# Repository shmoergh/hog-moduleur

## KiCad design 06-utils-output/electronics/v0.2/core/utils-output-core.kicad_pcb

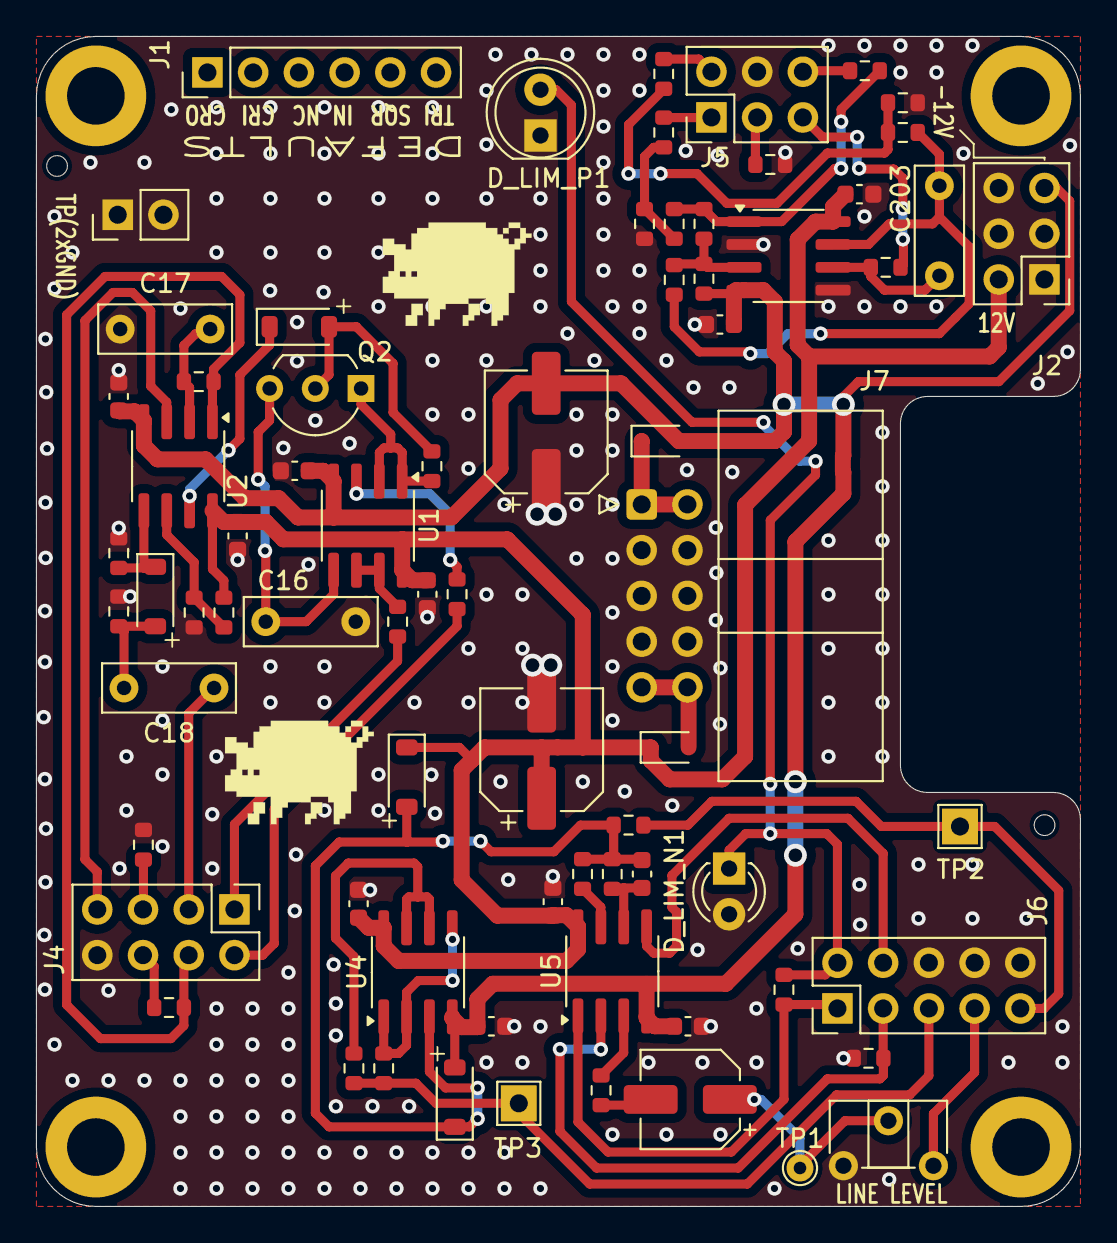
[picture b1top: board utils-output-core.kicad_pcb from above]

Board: 2 copper layers, 58.0 x 65.0 mm, 77 parts (0 on the bottom side), 48 nets.

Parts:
C1, C2, C3, C4, C10, C11, C12, C13, C201, C202: 100n; C_0603_1608Metric
C8, C9: 100u; CP_Elec_6.3x7.7
C14: 10u; CP_Elec_5x5.4
C15: 100p; C_0603_1608Metric
C16, C17: 100n (foil); C_Rect_L7.2mm_W2.5mm_P5.00mm_FKS2_FKP2_MKS2_MKP2
C18: 1n (foil); C_Rect_L7.2mm_W2.5mm_P5.00mm_FKS2_FKP2_MKS2_MKP2
C203: 3.3n (foil); C_Rect_L7.0mm_W2.5mm_P5.00mm
D1, D2: 1N5817; D_SOD-323
D3, D4, D15, D16: 1N4148; D_SOD-123
D_LIM_N1: Red LED; LED_D3.0mm
D_LIM_P1: Red LED; LED_D5.0mm
H1, H2, H3, H4: MountingHole; MountingHole_3.2mm_M3_DIN965_Pad
J1: Conn_01x06; PinHeader_1x06_P2.54mm_Vertical
J2, J5: Conn_02x03_Odd_Even; PinHeader_2x03_P2.54mm_Vertical
J3: Conn_01x02; PinHeader_1x02_P2.54mm_Vertical
J4: Conn_02x04_Odd_Even; PinHeader_2x04_P2.54mm_Vertical
J6: Conn_02x05_Odd_Even; PinHeader_2x05_P2.54mm_Vertical
J7: Conn_02x05_Odd_Even; IDC-Header_2x05_P2.54mm_Horizontal
Q2: 2N3819; TO-92_Inline_Wide
R1: 33k; R_0603_1608Metric
R10, R18, R29, R211: 10k; R_0603_1608Metric
R11, R20: 4.7k; R_0603_1608Metric
R12: 150; R_0603_1608Metric
R13, R17, R25, R208, R212: 1k; R_0603_1608Metric
R14, R15: 100; R_0603_1608Metric
R16, R209: 1M; R_0603_1608Metric
R19, R21, R22, R23, R205: 100k; R_0603_1608Metric
R24: 22k; R_0603_1608Metric
R201: 5.1M; R_0603_1608Metric
R202: 200k; R_0603_1608Metric
R203: 15k; R_0603_1608Metric
R204: 470k; R_0603_1608Metric
R206: 220; R_0603_1608Metric
R207: 12k; R_0603_1608Metric
R210: 2k; R_0603_1608Metric
RV_LINE_OUT_LVL1: 10k; Potentiometer_ACP_CA6-H2,5_Horizontal
TP1: MAX_LINEOUT; TestPoint_THTPad_D1.5mm_Drill0.7mm
TP2: MAINOUT; TestPoint_THTPad_2.0x2.0mm_Drill1.0mm
TP3: PHONES_OUT; TestPoint_THTPad_2.0x2.0mm_Drill1.0mm
U1, U2, U5, U201: TL072; SOIC-8_3.9x4.9mm_P1.27mm
U4: NE5532; SOIC-8_3.9x4.9mm_P1.27mm

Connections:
+12V: C1.1, C3.1, C8.1, C10.1, C12.1, C201.1, D1.1 (K), D15.1 (K), J2.2, R22.2, U1.8 (V+), U2.8 (V+), U4.8 (V+), U5.8 (V+), U201.8 (V+)
-12V: C2.2, C4.2, C9.2, C11.2, C13.2, C202.2, D2.2 (A), D16.2 (A), J2.5, R201.1, U1.4 (V-), U2.4 (V-), U4.4 (V-), U5.4 (V-), U201.4 (V-)
CRUSH_IN: J4.2, R10.1
CRUSH_OUT: J4.1, R17.2
CRUSH_TRIG: C18.1, J4.3
CRUSH_TRIG_DEFAULT: J4.4, R18.2, R19.2, U2.1
GND: C1.2, C2.1, C3.2, C4.1, C8.2, C9.1, C10.2, C11.1, C12.2, C13.1, C16.2, C17.2, C201.2, C202.1, D_LIM_N1.2 (A), D_LIM_P1.1 (K), J2.1, J2.3, J2.4, J2.6, J3.1, J3.2, J4.8, J5.4, J6.6, J6.8, J6.10, J7.3, J7.4, J7.5, J7.6, J7.7, J7.8, R1.1, R20.1, R21.1, R23.1, R24.1, R206.2, R207.2, R211.2, RV_LINE_OUT_LVL1.1, U201.2 (-), U201.5 (+)
LFO_POT_1: J5.3, R206.1
LFO_POT_2: J5.5, R209.2
LFO_POT_3: J5.6, R204.1
LFO_SQR: J5.1, R208.2
LFO_TRI: J5.2, R212.2
unnamed: R17.1, U1.6 (-), U1.7
unnamed: R10.2, U1.3 (+)
unnamed: R29.1, U5.3 (+)
unnamed: C14.1, RV_LINE_OUT_LVL1.2, TP1.1
unnamed: C14.2, R29.2
unnamed: C203.1, R205.2, R210.1, U201.7
unnamed: D1.2 (A), J7.9, J7.10
unnamed: D2.1 (K), J7.1, J7.2
unnamed: C18.2, D3.2 (A), R21.2
unnamed: D3.1 (K), R23.2, U2.5 (+)
unnamed: D4.2 (A), Q2.2 (G), R16.1
unnamed: D4.1 (K), U2.7
unnamed: C15.2, D15.2 (A), D16.1 (K), R11.1, R12.1, R13.1, U4.3 (+)
unnamed: Q2.1 (D), R16.2, U1.1, U1.2 (-)
unnamed: C16.1, Q2.3 (S), U1.5 (+)
unnamed: R12.2, U5.7
unnamed: R202.2, R203.1, R204.2, U201.1
unnamed: R203.2, R207.1, R208.1
unnamed: R210.2, R211.1, R212.1
unnamed: C17.1, R18.1, U2.2 (-)
unnamed: R1.2, R22.1, U2.6 (-)
unnamed: R15.2, U4.1, U4.2 (-), U4.5 (+)
unnamed: R14.2, U4.6 (-), U4.7
unnamed: C15.1, R11.2, U5.6 (-)
unnamed: R201.2, R202.1, R205.1, U201.3 (+)
unnamed: C203.2, R209.1, U201.6 (-)
OUTPUT_DRIVE_1: J6.3, R24.2, U5.2 (-)
OUTPUT_DRIVE_3: J6.1, R25.2, U5.1
OUTPUT_IN: J6.7, RV_LINE_OUT_LVL1.3
OUTPUT_LINE_OUT: J6.9, R13.2, TP2.1
OUTPUT_PHONES_OUT: J6.5, R14.1, R15.1, TP3.1
OUTPUT_VOL_2: J6.4, U5.5 (+)
OUTPUT_VOL_3: D_LIM_N1.1 (K), D_LIM_P1.2 (A), J6.2, R25.1
RV_CRUSH_1: J4.5, R20.2
RV_CRUSH_2: J4.7, U2.3 (+)
RV_CRUSH_3: J4.6, R19.1

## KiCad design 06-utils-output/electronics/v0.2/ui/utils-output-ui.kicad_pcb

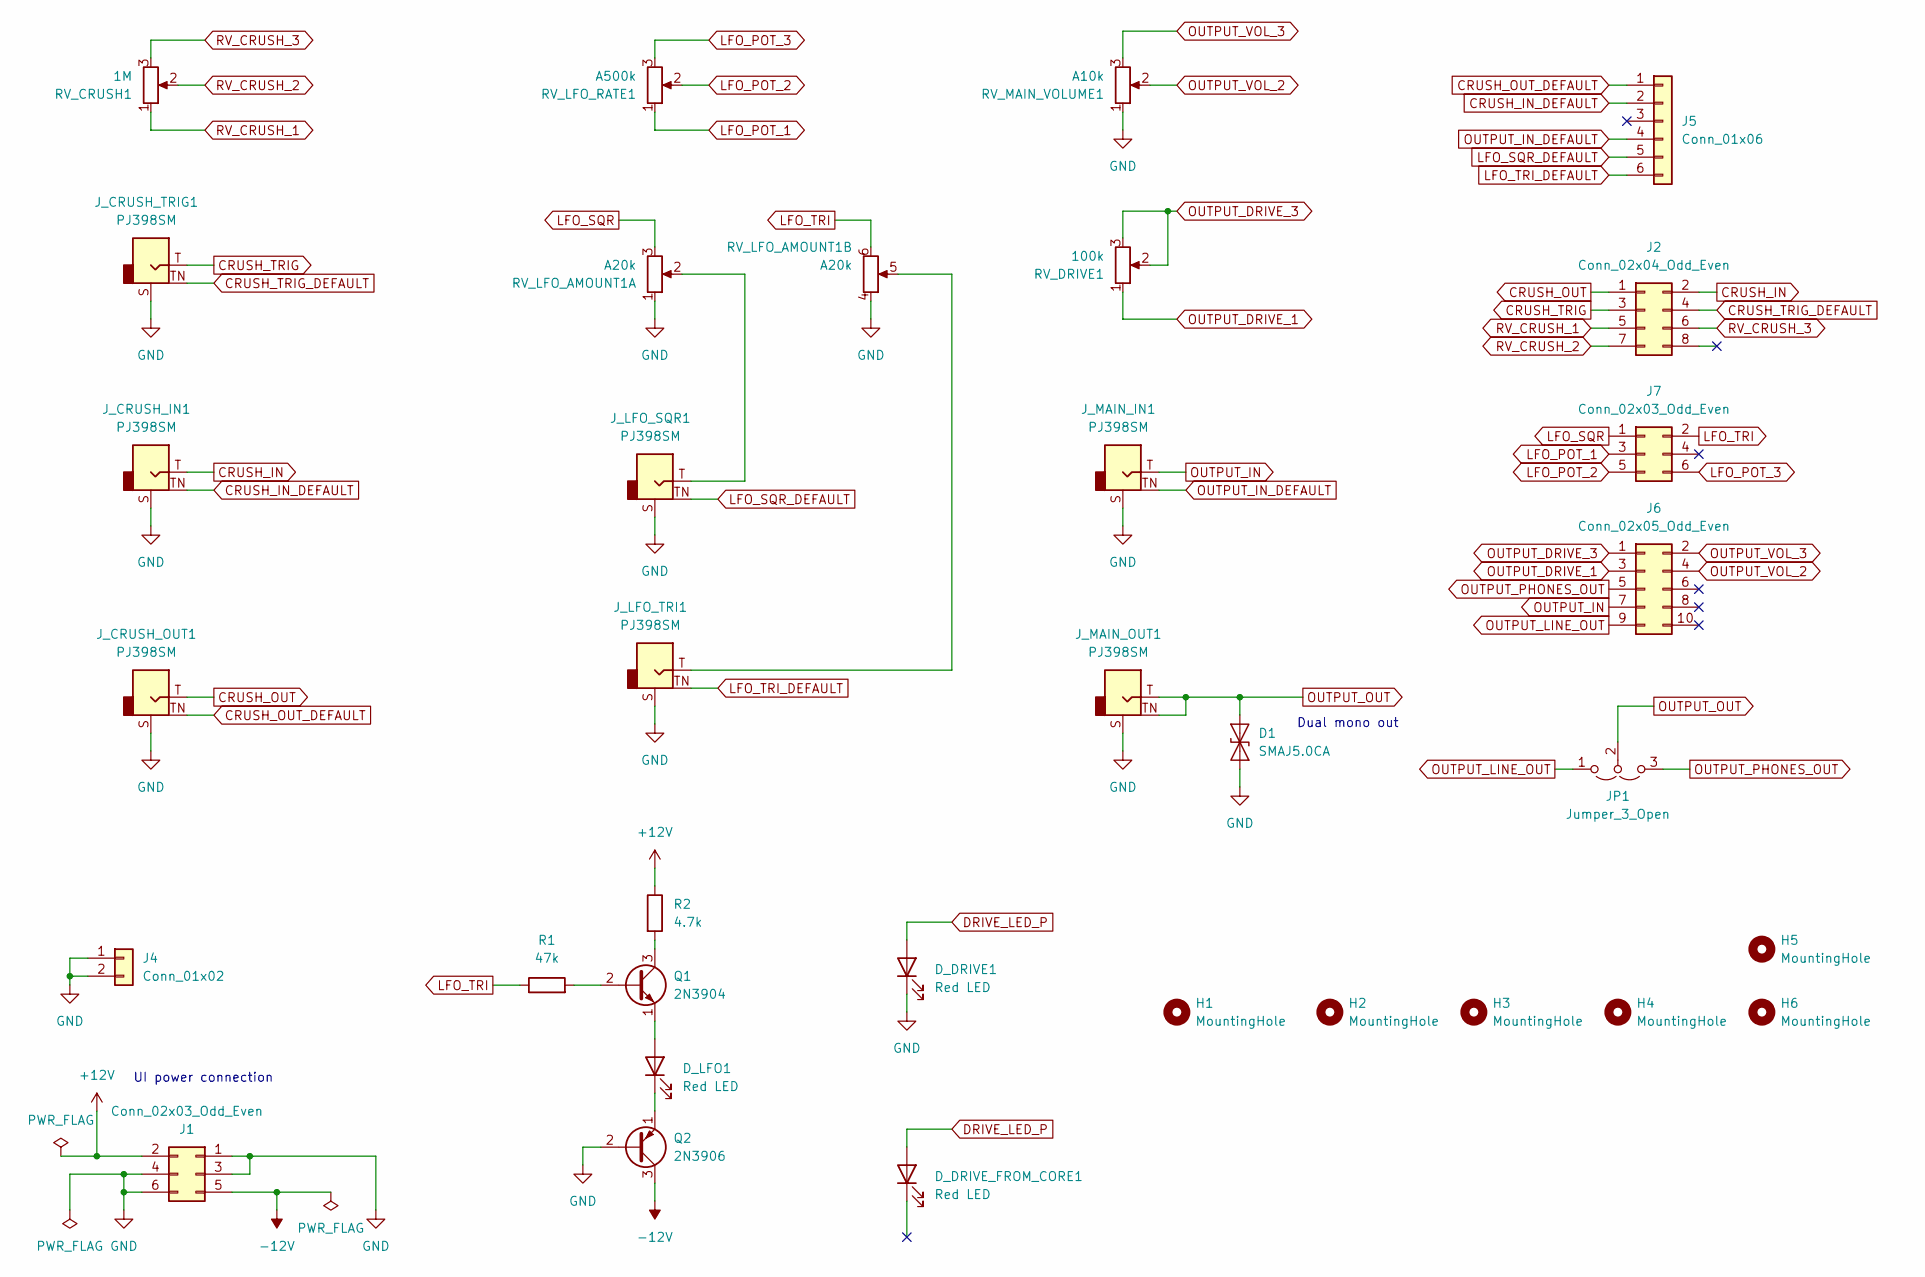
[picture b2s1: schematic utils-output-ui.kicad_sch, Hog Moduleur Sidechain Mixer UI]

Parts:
D1: SMAJ5.0CA; D_SMA
D_DRIVE1: Red LED; LED_D3.0mm
D_DRIVE_FROM_CORE1: Red LED; PinSocket_1x02_P2.54mm_Vertical
D_LFO1: Red LED; LED_D3.0mm
H1, H2, H3, H4, H5, H6: MountingHole; MountingHole_3.2mm_M3_DIN965_Pad
J1: Conn_02x03_Odd_Even; PinSocket_2x03_P2.54mm_Vertical; Part no. 200-SSW10301TD
J2: Conn_02x04_Odd_Even; PinSocket_2x04_P2.54mm_Vertical
J4: Conn_01x02; PinSocket_1x02_P2.54mm_Vertical; Part no. 200-SSW10201TS
J5: Conn_01x06; PinSocket_1x06_P2.54mm_Vertical; Part no. 200-SSW10601TS
J6: Conn_02x05_Odd_Even; PinSocket_2x05_P2.54mm_Vertical
J7: Conn_02x03_Odd_Even; PinSocket_2x03_P2.54mm_Vertical
JP1: Jumper_3_Open; PinHeader_1x03_P2.54mm_Horizontal
J_CRUSH_IN1: PJ398SM; Jack_3.5mm_QingPu_WQP-PJ398SM_Vertical_CircularHoles; Part no. PJ398SM
J_CRUSH_OUT1: PJ398SM; Jack_3.5mm_QingPu_WQP-PJ398SM_Vertical_CircularHoles; Part no. PJ398SM
J_CRUSH_TRIG1: PJ398SM; Jack_3.5mm_QingPu_WQP-PJ398SM_Vertical_CircularHoles; Part no. PJ398SM
J_LFO_SQR1: PJ398SM; Jack_3.5mm_QingPu_WQP-PJ398SM_Vertical_CircularHoles; Part no. PJ398SM
J_LFO_TRI1: PJ398SM; Jack_3.5mm_QingPu_WQP-PJ398SM_Vertical_CircularHoles; Part no. PJ398SM
J_MAIN_IN1: PJ398SM; Jack_3.5mm_QingPu_WQP-PJ398SM_Vertical_CircularHoles; Part no. PJ398SM
J_MAIN_OUT1: PJ398SM; Jack_3.5mm_QingPu_WQP-PJ398SM_Vertical_CircularHoles; Part no. PJ398SM
Q1: 2N3904; TO-92_Inline_Wide
Q2: 2N3906; TO-92_Inline_Wide
R1: 47k; R_Axial_DIN0207_L6.3mm_D2.5mm_P7.62mm_Horizontal
R2: 4.7k; R_Axial_DIN0207_L6.3mm_D2.5mm_P7.62mm_Horizontal
RV_CRUSH1: 1M; Potentiometer_Bourns_Single-PTV09A; Part no. 652-PTV09A4025FB104
RV_DRIVE1: 100k; Potentiometer_Bourns_Single-PTV09A; Part no. 652-PTV09A4025FB104
RV_LFO_AMOUNT1: A20k; Potentiometer_Bourns_Dual-PTV112-4; Part No. 652-PTV1124425AA203
RV_LFO_RATE1: A500k; Potentiometer_Bourns_Single-PTV09A; Part no. 652-PTV09A4025FB104
RV_MAIN_VOLUME1: A10k; Potentiometer_Bourns_Single-PTV09A; Part no. 652-PTV09A4025FB104

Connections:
+12V: J1.2, R2.1
-12V: J1.5, Q2.3 (C)
CRUSH_IN: J2.2, J_CRUSH_IN1.T
CRUSH_IN_DEFAULT: J5.2, J_CRUSH_IN1.TN
CRUSH_OUT: J2.1, J_CRUSH_OUT1.T
CRUSH_OUT_DEFAULT: J5.1, J_CRUSH_OUT1.TN
CRUSH_TRIG: J2.3, J_CRUSH_TRIG1.T
CRUSH_TRIG_DEFAULT: J2.4, J_CRUSH_TRIG1.TN
DRIVE_LED_P: D_DRIVE1.2 (A), D_DRIVE_FROM_CORE1.2 (A)
GND: D1.1 (A1), D_DRIVE1.1 (K), J1.1, J1.3, J1.4, J1.6, J4.1, J4.2, J_CRUSH_IN1.S, J_CRUSH_OUT1.S, J_CRUSH_TRIG1.S, J_LFO_SQR1.S, J_LFO_TRI1.S, J_MAIN_IN1.S, J_MAIN_OUT1.S, Q2.2 (B), RV_LFO_AMOUNT1.1, RV_LFO_AMOUNT1.4, RV_MAIN_VOLUME1.1
LFO_POT_1: J7.3, RV_LFO_RATE1.1
LFO_POT_2: J7.5, RV_LFO_RATE1.2
LFO_POT_3: J7.6, RV_LFO_RATE1.3
LFO_SQR: J7.1, RV_LFO_AMOUNT1.3
LFO_SQR_DEFAULT: J5.5, J_LFO_SQR1.TN
LFO_TRI: J7.2, R1.1, RV_LFO_AMOUNT1.6
LFO_TRI_DEFAULT: J5.6, J_LFO_TRI1.TN
unnamed: D_LFO1.2 (A), Q1.1 (E)
unnamed: D_LFO1.1 (K), Q2.1 (E)
unnamed: J_LFO_SQR1.T, RV_LFO_AMOUNT1.2
unnamed: J_LFO_TRI1.T, RV_LFO_AMOUNT1.5
unnamed: Q1.2 (B), R1.2
unnamed: Q1.3 (C), R2.2
OUTPUT_DRIVE_1: J6.3, RV_DRIVE1.1
OUTPUT_DRIVE_3: J6.1, RV_DRIVE1.2, RV_DRIVE1.3
OUTPUT_IN: J6.7, J_MAIN_IN1.T
OUTPUT_IN_DEFAULT: J5.4, J_MAIN_IN1.TN
OUTPUT_LINE_OUT: J6.9, JP1.1 (A)
OUTPUT_OUT: D1.2 (A2), JP1.2 (C), J_MAIN_OUT1.T, J_MAIN_OUT1.TN
OUTPUT_PHONES_OUT: J6.5, JP1.3 (B)
OUTPUT_VOL_2: J6.4, RV_MAIN_VOLUME1.2
OUTPUT_VOL_3: J6.2, RV_MAIN_VOLUME1.3
RV_CRUSH_1: J2.5, RV_CRUSH1.1
RV_CRUSH_2: J2.7, RV_CRUSH1.2
RV_CRUSH_3: J2.6, RV_CRUSH1.3

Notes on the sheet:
Dual mono out
UI power connection

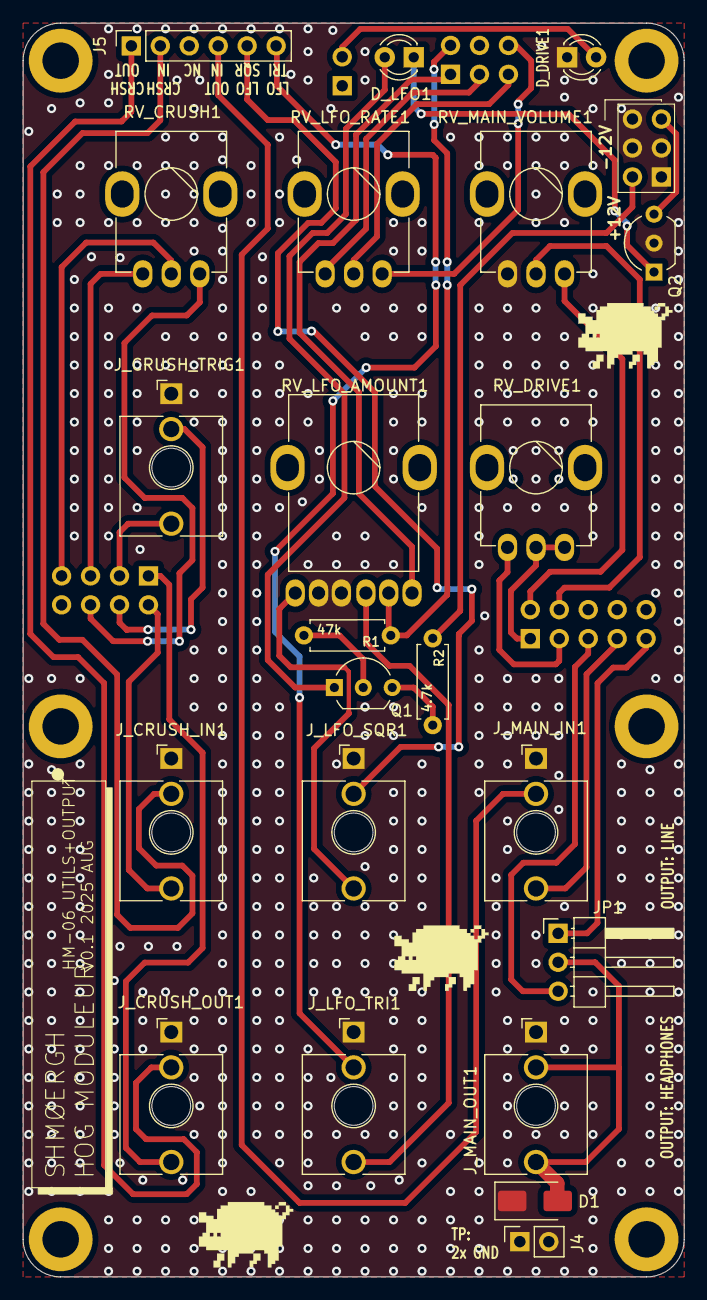
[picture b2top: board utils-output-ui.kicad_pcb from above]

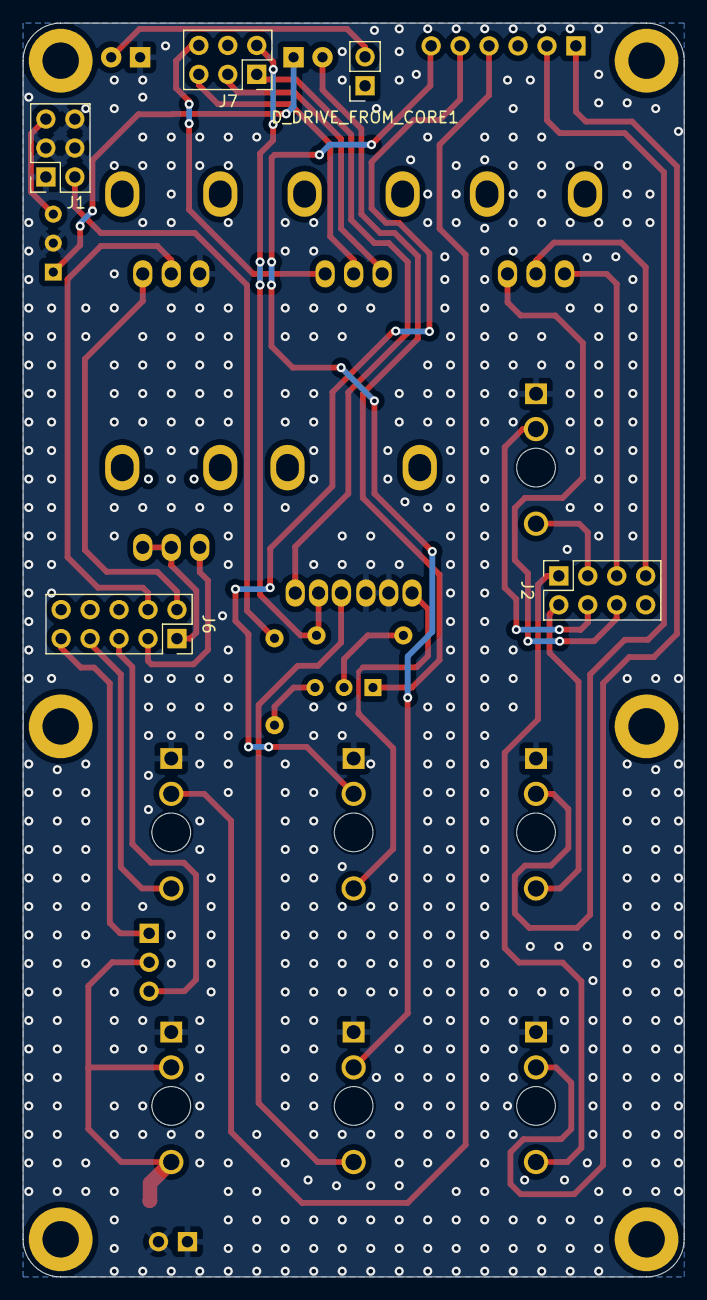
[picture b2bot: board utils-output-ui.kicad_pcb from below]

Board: 2 copper layers, 58.0 x 110.0 mm, 33 parts (5 on the bottom side), 35 nets.

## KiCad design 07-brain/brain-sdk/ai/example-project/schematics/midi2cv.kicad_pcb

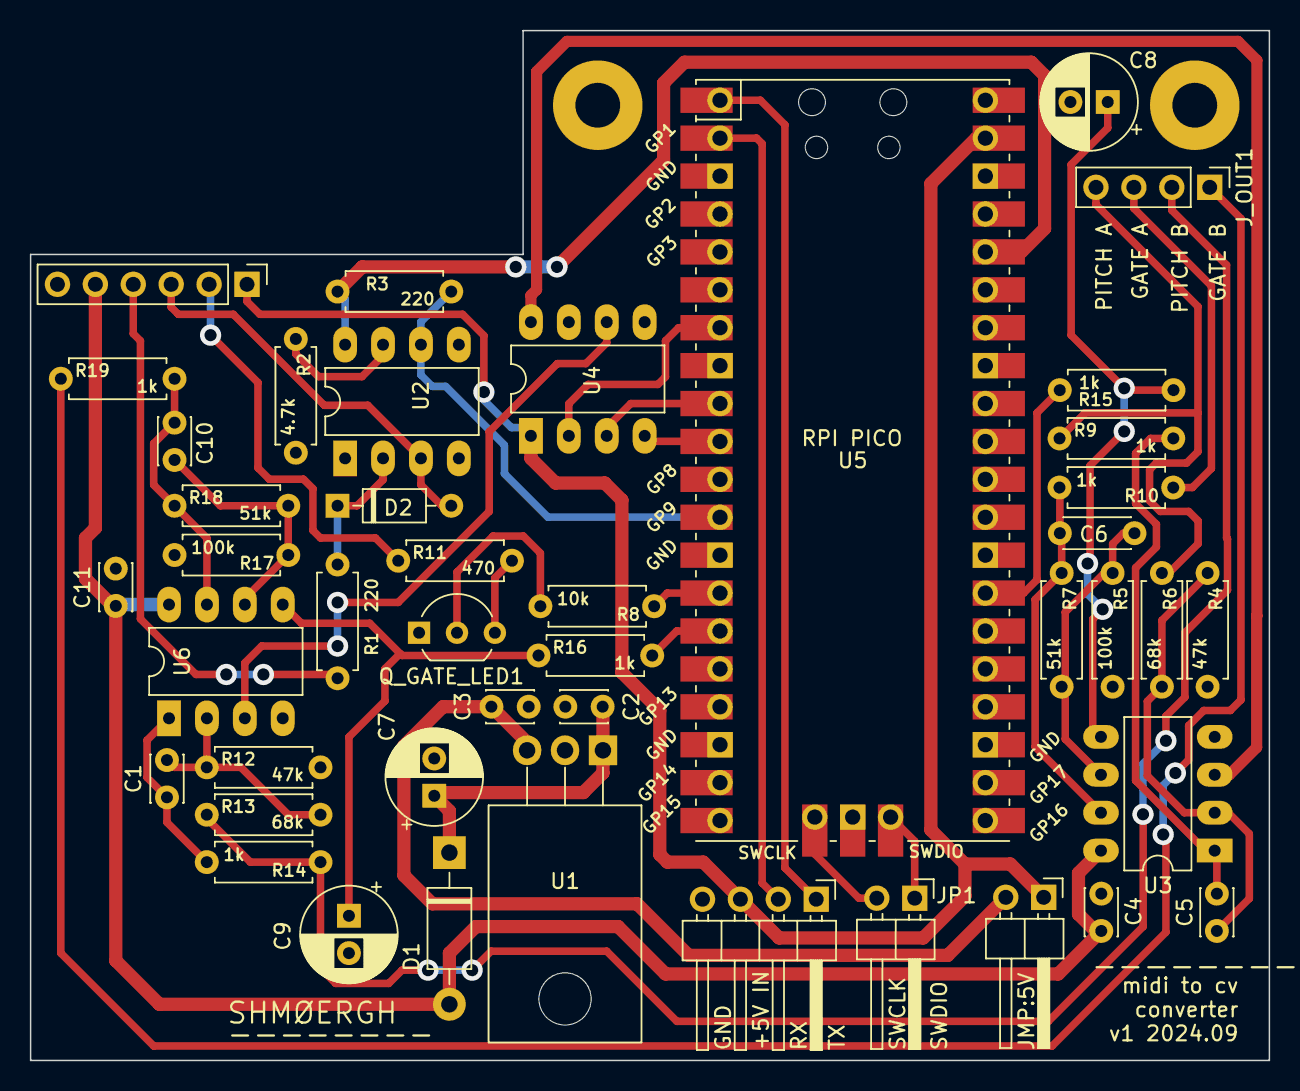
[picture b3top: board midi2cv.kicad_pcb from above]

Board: 2 copper layers, 83.0 x 69.0 mm, 46 parts (0 on the bottom side), 40 nets.

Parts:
C1, C5, C10: 22p; C_Disc_D3.0mm_W2.0mm_P2.50mm
C2: 330n; C_Disc_D3.0mm_W2.0mm_P2.50mm
C3, C4, C11: 100n; C_Disc_D3.0mm_W2.0mm_P2.50mm
C6: 22p; C_Disc_D4.3mm_W1.9mm_P5.00mm
C7: 10u; CP_Radial_D6.3mm_P2.50mm
C8, C9: 1u; CP_Radial_D6.3mm_P2.50mm
D1: 1N4001; D_DO-41_SOD81_P10.16mm_Horizontal
D2: 1N4148; D_DO-35_SOD27_P7.62mm_Horizontal
H1, H2: MountingHole; MountingHole_3mm_Pad
JP1: Jumper_2_Open; PinHeader_1x02_P2.54mm_Horizontal
J_IN1: Conn_01x06; PinHeader_1x06_P2.54mm_Vertical
J_OUT1: Conn_01x04; PinHeader_1x04_P2.54mm_Vertical
J_SWCLKDIO1: Conn_01x02; PinHeader_1x02_P2.54mm_Horizontal
J_SWD_IO1: Conn_01x04; PinHeader_1x04_P2.54mm_Horizontal
Q_GATE_LED1: 2N3904; TO-92_Inline_Wide
R1, R3: 220; R_Axial_DIN0207_L6.3mm_D2.5mm_P7.62mm_Horizontal
R2: 4.7k; R_Axial_DIN0207_L6.3mm_D2.5mm_P7.62mm_Horizontal
R4, R12: 47k; R_Axial_DIN0207_L6.3mm_D2.5mm_P7.62mm_Horizontal
R5, R17: 100k; R_Axial_DIN0207_L6.3mm_D2.5mm_P7.62mm_Horizontal
R6, R13: 68k; R_Axial_DIN0207_L6.3mm_D2.5mm_P7.62mm_Horizontal
R7, R18: 51k; R_Axial_DIN0207_L6.3mm_D2.5mm_P7.62mm_Horizontal
R8: 10k; R_Axial_DIN0207_L6.3mm_D2.5mm_P7.62mm_Horizontal
R9, R10, R14, R15, R16, R19: 1k; R_Axial_DIN0207_L6.3mm_D2.5mm_P7.62mm_Horizontal
R11: 470; R_Axial_DIN0207_L6.3mm_D2.5mm_P7.62mm_Horizontal
U1: LM7805_TO220; TO-220-3_Horizontal_TabDown
U2: 6N138; DIP-8_W7.62mm_LongPads
U3, U6: LM358; DIP-8_W7.62mm_LongPads
U4: MCP4822; DIP-8_W7.62mm_LongPads
U5: Pico; RPi_Pico_SMD_TH

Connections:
+3.3V: R3.1, U2.8 (VCC), U5.36 (3V3)
+5V: JP1.1 (A), J_IN1.1, J_SWD_IO1.3, U4.1 (Vdd), U5.39 (VSYS)
+12V: C4.1, C11.1, D1.2 (A), J_IN1.5, U3.8 (V+), U6.8 (V+)
DAC_A: U3.3 (+), U4.8 (VA)
DAC_B: U4.6 (VB), U6.3 (+)
DAC_CS: U4.2 (~CS), U5.7 (GPIO5)
DAC_SCK: U4.3 (SCK), U5.9 (GPIO6)
DAC_SDI: U4.4 (SDI), U5.10 (GPIO7)
GATE_A: J_OUT1.3, R10.1
GATE_A_TRIG: R15.2, U5.27 (GPIO21)
GATE_B: J_OUT1.1, R19.1
GATE_B_TRIG: R16.2, U5.15 (GPIO11)
GND: C2.2, C3.2, C4.2, C7.2, C8.2, C9.2, C11.2, J_IN1.6, J_SWD_IO1.4, Q_GATE_LED1.1 (E), R2.2, R4.2, R5.2, R12.2, R17.2, U1.2 (GND), U2.5 (GND), U3.4 (V-), U4.5 (~LDAC), U4.7 (Vss), U5.3 (GND), U5.8 (GND), U5.13 (GND), U5.18 (GND), U5.23 (GND), U5.28 (GND), U5.38 (GND), U6.4 (V-)
LED_GND: J_IN1.2, R11.1
LED_OUT: R8.1, U5.14 (GPIO10)
MIDI_4R: J_IN1.4, R1.2
MIDI_5T: D2.2 (A), J_IN1.3, U2.3 (C2)
MIDI_IN: R3.2, U2.6 (VO2), U5.12 (GPIO9)
unnamed: C1.1, R14.2, U6.1
unnamed: C5.1, R9.2, U3.1
unnamed: C6.1, R7.1, R10.2, U3.7
unnamed: C10.1, R18.1, R19.2, U6.7
unnamed: C2.1, C7.1, D1.1 (K), U1.1 (VI)
unnamed: D2.1 (K), R1.1, U2.2 (C1)
unnamed: C3.1, JP1.2 (B), U1.3 (VO)
unnamed: J_SWCLKDIO1.1, U5.43 (SWDIO)
unnamed: J_SWCLKDIO1.2, U5.41 (SWCLK)
unnamed: Q_GATE_LED1.2 (B), R8.2
unnamed: Q_GATE_LED1.3 (C), R11.2
unnamed: R2.1, U2.7 (VO1)
unnamed: C5.2, R4.1, R6.2, U3.2 (-)
unnamed: C8.1, R15.1, U3.5 (+)
unnamed: C6.2, R5.1, R7.2, U3.6 (-)
unnamed: C1.2, R12.1, R13.2, U6.2 (-)
unnamed: C9.1, R16.1, U6.5 (+)
unnamed: C10.2, R17.1, R18.2, U6.6 (-)
PITCH_A: J_OUT1.4, R6.1, R9.1
PITCH_B: J_OUT1.2, R13.1, R14.1
UART_RX: J_SWD_IO1.2, U5.2 (GPIO1)
UART_TX: J_SWD_IO1.1, U5.1 (GPIO0)

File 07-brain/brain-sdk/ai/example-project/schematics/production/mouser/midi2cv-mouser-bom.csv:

"Reference","Value","Datasheet","Footprint","Qty","DNP","Part No.","Part URL","Vendor"
"H1,H2","MountingHole","~","MountingHole:MountingHole_3mm_Pad","2","","","",""
"C1,C5,C6,C10","22p","~","-- mixed values --","4","","594-K220J15C0GF53L2 ","https://mou.sr/3ZTXYXB","Mouser"
"C2","330n","~","Capacitor_THT:C_Disc_D3.0mm_W2.0mm_P2.50mm","1","","810-FA14X7R1H334KNU6 ","https://mou.sr/4gDlMo9","Mouser"
"C3,C4,C11","100n","~","Capacitor_THT:C_Disc_D3.0mm_W2.0mm_P2.50mm","3","","594-K103K15X7RF5TK2 ","https://mou.sr/3VFZIRH","Mouser"
"C7","10u","~","Capacitor_THT:CP_Radial_D6.3mm_P2.50mm","1","","80-ESS106M035AC2EA ","https://mou.sr/49DyMaU","Mouser"
"C8,C9","1u","~","Capacitor_THT:CP_Radial_D6.3mm_P2.50mm","2","","140-SG1R0M1H0407P ","https://mou.sr/41BqE8O","Mouser"
"D1","1N4001","~","Diode_THT:D_DO-41_SOD81_P10.16mm_Horizontal","1","","637-1N4001 ","https://mou.sr/3DfEJyK","Mouser"
"D2","1N4148","~","Diode_THT:D_DO-35_SOD27_P7.62mm_Horizontal","1","","512-1N4148 ","https://mou.sr/3ZP7Wt3","Mouser"
"JP1","Jumper_2_Open","~","Connector_PinHeader_2.54mm:PinHeader_1x02_P2.54mm_Horizontal","1","","737-PH1RB-02-UA ","https://mou.sr/3D93YT9","Mouser"
"J_IN1","Conn_01x06","~","Connector_PinHeader_2.54mm:PinHeader_1x06_P2.54mm_Vertical","1","","737-RS1-06-G ","https://mou.sr/3BuZUME","Mouser"
"J_OUT1,J_SWD_IO1","Conn_01x04","~","-- mixed values --","2","","737-RS1-04-G ","https://mou.sr/4gDjs0p","Mouser"
"J_SWCLKDIO1","Conn_01x02","~","Connector_PinHeader_2.54mm:PinHeader_1x02_P2.54mm_Horizontal","1","","737-PH1RB-02-UA ","https://mou.sr/3D93YT9","Mouser"
"Q_GATE_LED1","2N3904","https://www.onsemi.com/pub/Collateral/2N3903-D.PDF","Package_TO_SOT_THT:TO-92_Inline_Wide","1","","637-2N3904 ","https://mou.sr/4febysZ","Mouser"
"R1,R3","220","~","Shmoergh_Custom_Footprints:R_Axial_DIN0207_L6.3mm_D2.5mm_P7.62mm_Horizontal","2","","603-MFR-25FTF52-220R","https://mou.sr/41wmEVF","Mouser"
"R2","4.7k","~","Shmoergh_Custom_Footprints:R_Axial_DIN0207_L6.3mm_D2.5mm_P7.62mm_Horizontal","1","","603-MFR-25FBF52-4K7","https://mou.sr/4i8N07f","Mouser"
"R4,R12","47k","~","Shmoergh_Custom_Footprints:R_Axial_DIN0207_L6.3mm_D2.5mm_P7.62mm_Horizontal","2","","603-MFR-25FBF52-47K","https://mou.sr/3XWs8rz","Mouser"
"R5,R17","100k","~","Shmoergh_Custom_Footprints:R_Axial_DIN0207_L6.3mm_D2.5mm_P7.62mm_Horizontal","2","","603-MFR-25FRF52100K","https://mou.sr/4hEwI4G","Mouser"
"R6,R13","68k","~","Shmoergh_Custom_Footprints:R_Axial_DIN0207_L6.3mm_D2.5mm_P7.62mm_Horizontal","2","","603-MFR-25FBF52-68K","https://mou.sr/4gyTECt","Mouser"
"R7,R18","51k","~","Shmoergh_Custom_Footprints:R_Axial_DIN0207_L6.3mm_D2.5mm_P7.62mm_Horizontal","2","","603-MFR-25FBF52-51K","https://mou.sr/43NIOFo","Mouser"
"R8","10k","~","Shmoergh_Custom_Footprints:R_Axial_DIN0207_L6.3mm_D2.5mm_P7.62mm_Horizontal","1","","603-MFR25SFRF52-10K","https://mou.sr/3XU3MyE","Mouser"
"R9,R10,R14,R15,R16,R19","1k","~","Shmoergh_Custom_Footprints:R_Axial_DIN0207_L6.3mm_D2.5mm_P7.62mm_Horizontal","6","","603-MFR-25FBF52-1K","https://mou.sr/43MmrAb","Mouser"
"R11","470","~","Shmoergh_Custom_Footprints:R_Axial_DIN0207_L6.3mm_D2.5mm_P7.62mm_Horizontal","1","","603-MFR-25FBF52-470R","https://mou.sr/3XTF2Xk","Mouser"
"U1","LM7805_TO220","https://www.onsemi.cn/PowerSolutions/document/MC7800-D.PDF","Package_TO_SOT_THT:TO-220-3_Horizontal_TabDown","1","","926-LM7805CT/NOPB ","https://mou.sr/4gwivXu","Mouser"
"U2","6N138","http://www.onsemi.com/pub/Collateral/HCPL2731-D.pdf","Package_DIP:DIP-8_W7.62mm_LongPads","1","","859-6N138M ","https://mou.sr/3VDrRsD","Mouser"
"U3,U6","LM358","http://www.ti.com/lit/ds/symlink/lm2904-n.pdf","Package_DIP:DIP-8_W7.62mm_LongPads","2","","595-LM358P ","https://mou.sr/4izjQPc","Mouser"
"U4","MCP4822","http://ww1.microchip.com/downloads/en/DeviceDoc/20002249B.pdf","Package_DIP:DIP-8_W7.62mm_LongPads","1","","579-MCP4822-E/P ","https://mou.sr/4gecDm5","Mouser"
"U5","Pico","","MCU_RaspberryPi_and_Boards:RPi_Pico_SMD_TH","1","","358-SC0915 ","https://mou.sr/49BoTdS","Mouser"

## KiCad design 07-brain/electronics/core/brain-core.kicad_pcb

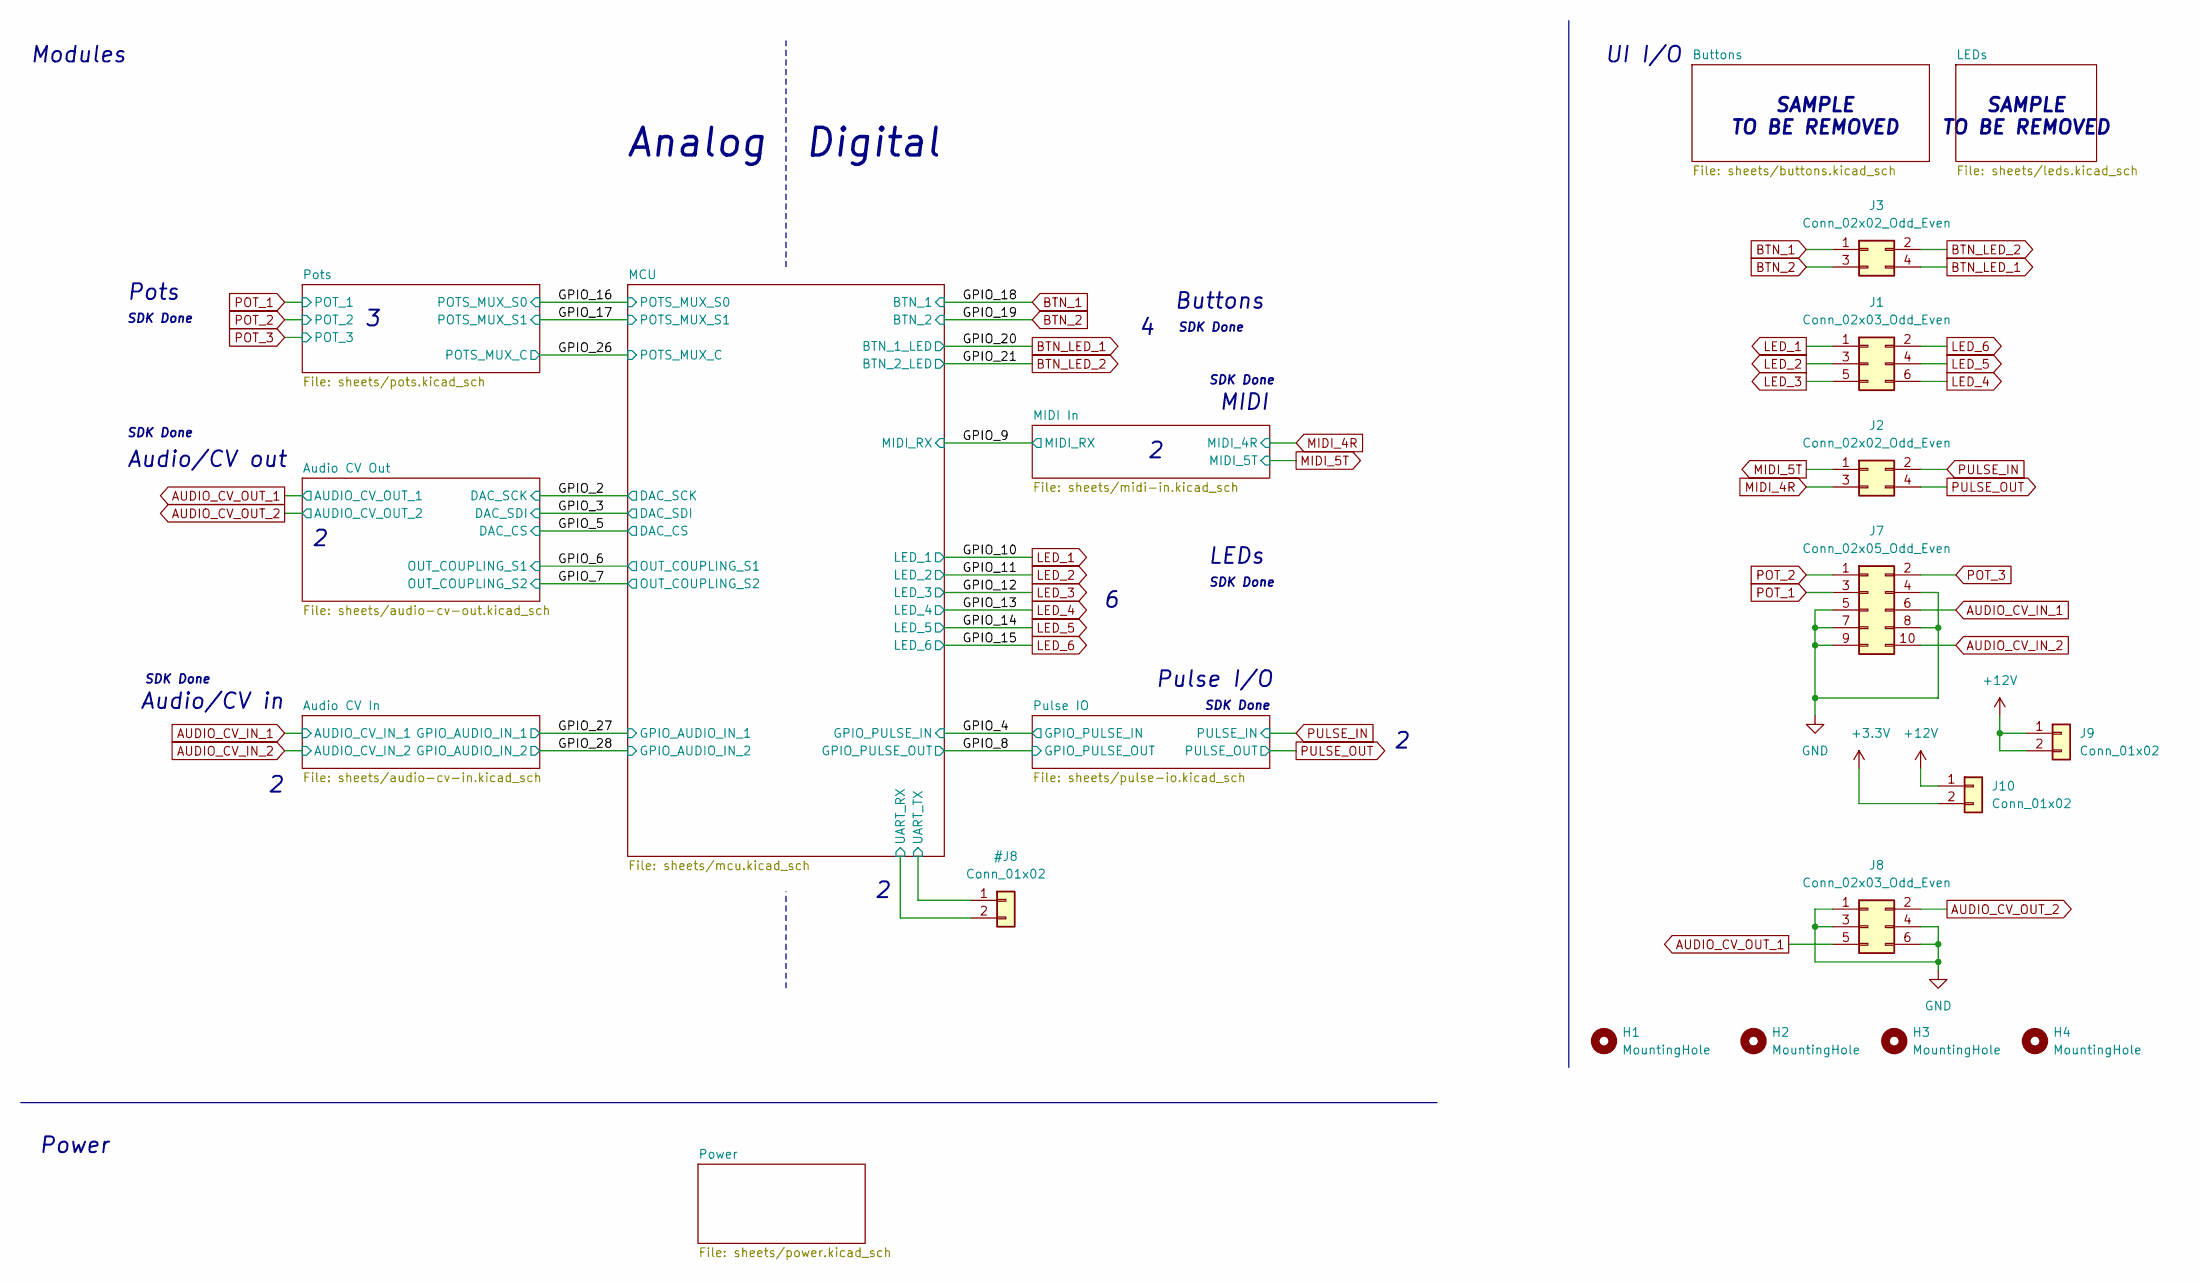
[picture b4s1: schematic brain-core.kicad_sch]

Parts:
H1, H2, H3, H4: MountingHole; MountingHole_3.2mm_M3_DIN965_Pad
J1, J8: Conn_02x03_Odd_Even; PinHeader_2x03_P2.54mm_Vertical
J2, J3: Conn_02x02_Odd_Even; PinHeader_2x02_P2.54mm_Vertical
J7: Conn_02x05_Odd_Even; PinHeader_2x05_P2.54mm_Vertical
J9, J10: Conn_01x02; PinHeader_1x02_P2.54mm_Vertical

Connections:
+12V: J9.1, J9.2, J10.1; also elsewhere on the board
AUDIO_CV_IN_1: J7.6; also elsewhere on the board
AUDIO_CV_IN_2: J7.10; also elsewhere on the board
AUDIO_CV_OUT_1: J8.5; also elsewhere on the board
AUDIO_CV_OUT_2: J8.2; also elsewhere on the board
BTN_1: J3.1; also elsewhere on the board
BTN_2: J3.3; also elsewhere on the board
BTN_LED_1: J3.4; also elsewhere on the board
BTN_LED_2: J3.2; also elsewhere on the board
LED_1: J1.1; also elsewhere on the board
LED_2: J1.3; also elsewhere on the board
LED_3: J1.5; also elsewhere on the board
LED_4: J1.6; also elsewhere on the board
LED_5: J1.4; also elsewhere on the board
LED_6: J1.2; also elsewhere on the board
POT_1: J7.3; also elsewhere on the board
POT_2: J7.1; also elsewhere on the board
POT_3: J7.2; also elsewhere on the board
PULSE_IN: J2.2; also elsewhere on the board
PULSE_OUT: J2.4; also elsewhere on the board

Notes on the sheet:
Power
Audio/CV in
SAMPLE TO BE REMOVED
Pulse I/O
Audio/CV out
SDK Done
LEDs
Modules
Buttons
Analog
Pots
Digital
MIDI
UI I/O

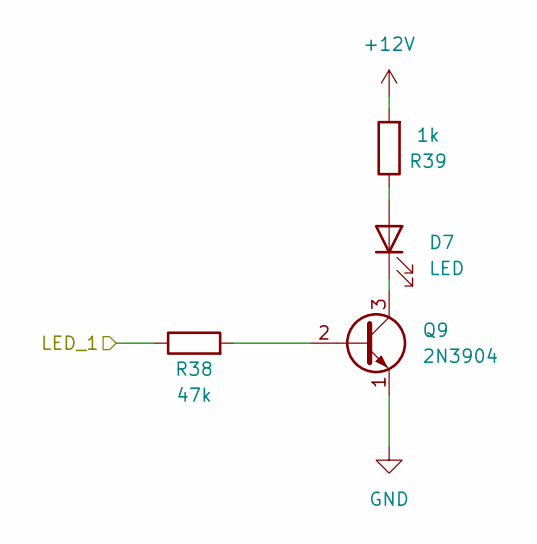
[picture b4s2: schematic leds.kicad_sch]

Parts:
D7: LED
Q9: 2N3904; TO-92_Inline
R38: 47k; R_0603_1608Metric; LCSC C25803
R39: 1k; R_0603_1608Metric

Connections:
unnamed: D7.1 (K), Q9.3 (C)
unnamed: D7.2 (A), R39.1
unnamed: Q9.2 (B), R38.2

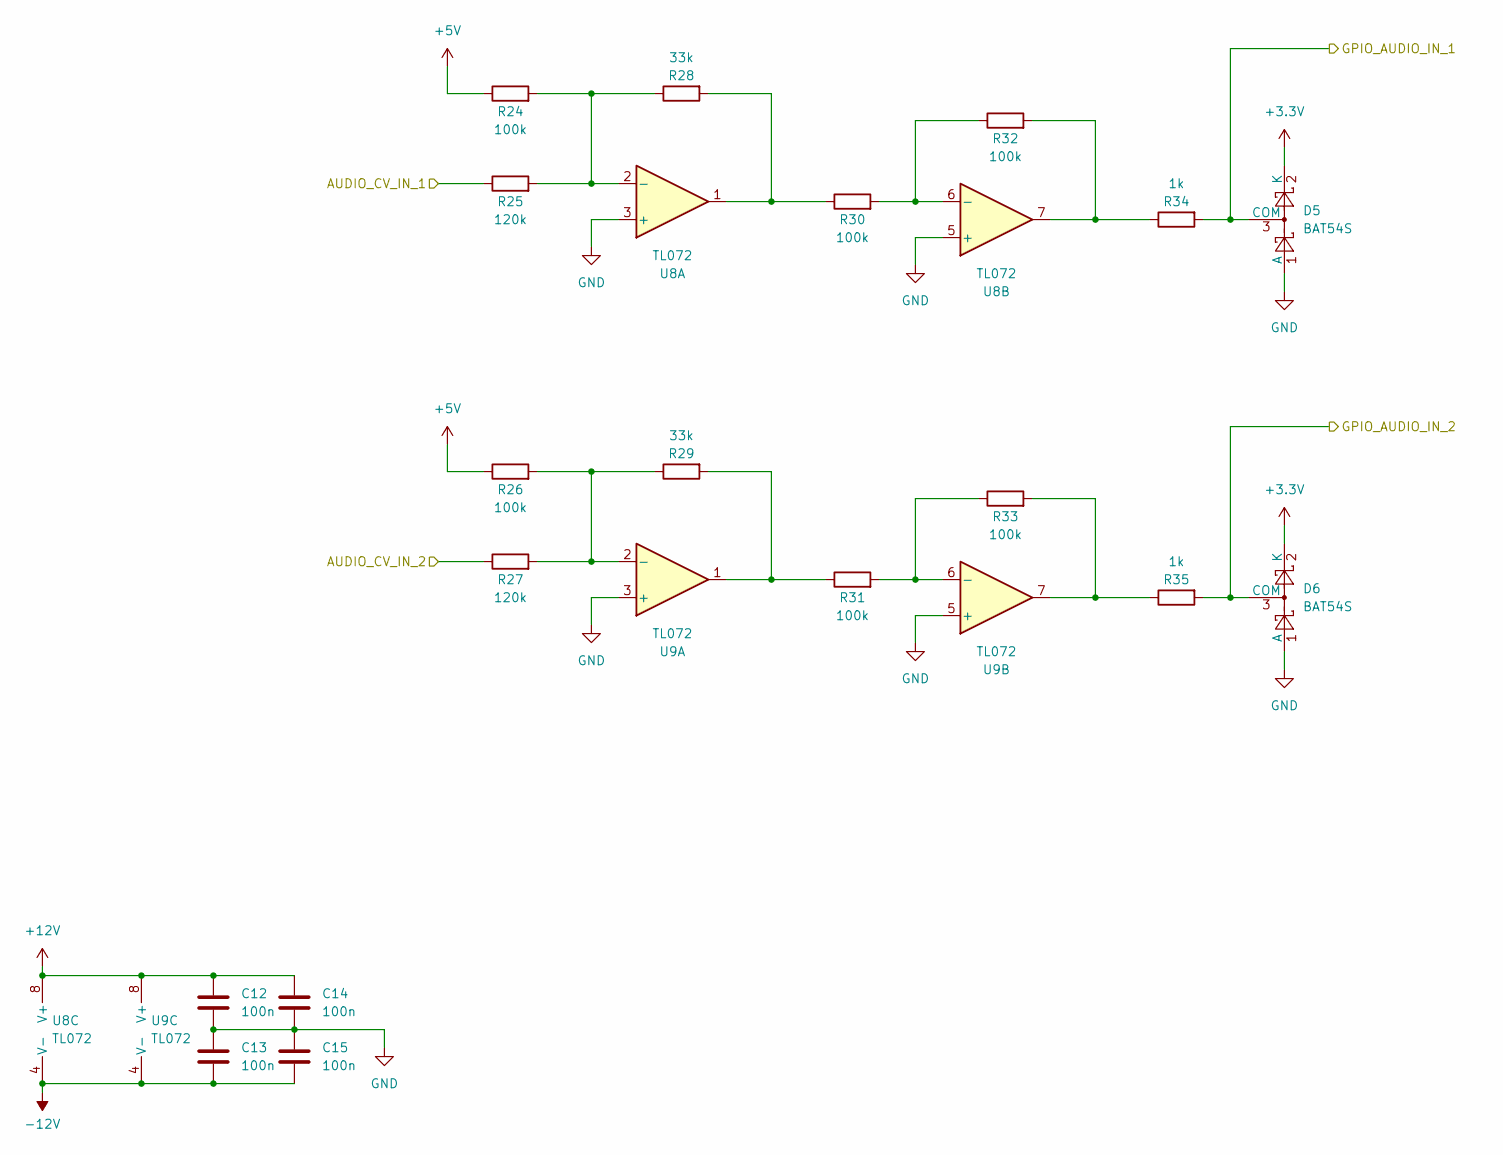
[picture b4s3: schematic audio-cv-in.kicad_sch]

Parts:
C12, C13, C14, C15: 100n; C_0603_1608Metric; LCSC C14663
D5, D6: BAT54S; SOT-23; LCSC C7420333
R24, R26, R30, R31, R32, R33: 100k; R_0603_1608Metric; LCSC C25803
R25, R27: 120k; R_0603_1608Metric
R28, R29: 33k; R_0603_1608Metric
R34, R35: 1k; R_0603_1608Metric
U8, U9: TL072; SOIC-8_3.9x4.9mm_P1.27mm

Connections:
+5V: R24.1, R26.1; also elsewhere on the board
+12V: C12.1, C14.1, U8.8 (V+), U9.8 (V+); also elsewhere on the board
-12V: C13.2, C15.2, U8.4 (V-), U9.4 (V-); also elsewhere on the board
/GPIO_27: D5.3 (COM), R34.2; also elsewhere on the board
/GPIO_28: D6.3 (COM), R35.2; also elsewhere on the board
AUDIO_CV_IN_1: R25.1; also elsewhere on the board
AUDIO_CV_IN_2: R27.1; also elsewhere on the board
unnamed: R28.2, R30.1, U8.1
unnamed: R29.2, R31.1, U9.1
unnamed: R32.2, R34.1, U8.7
unnamed: R33.2, R35.1, U9.7
unnamed: R24.2, R25.2, R28.1, U8.2 (-)
unnamed: R30.2, R32.1, U8.6 (-)
unnamed: R26.2, R27.2, R29.1, U9.2 (-)
unnamed: R31.2, R33.1, U9.6 (-)
